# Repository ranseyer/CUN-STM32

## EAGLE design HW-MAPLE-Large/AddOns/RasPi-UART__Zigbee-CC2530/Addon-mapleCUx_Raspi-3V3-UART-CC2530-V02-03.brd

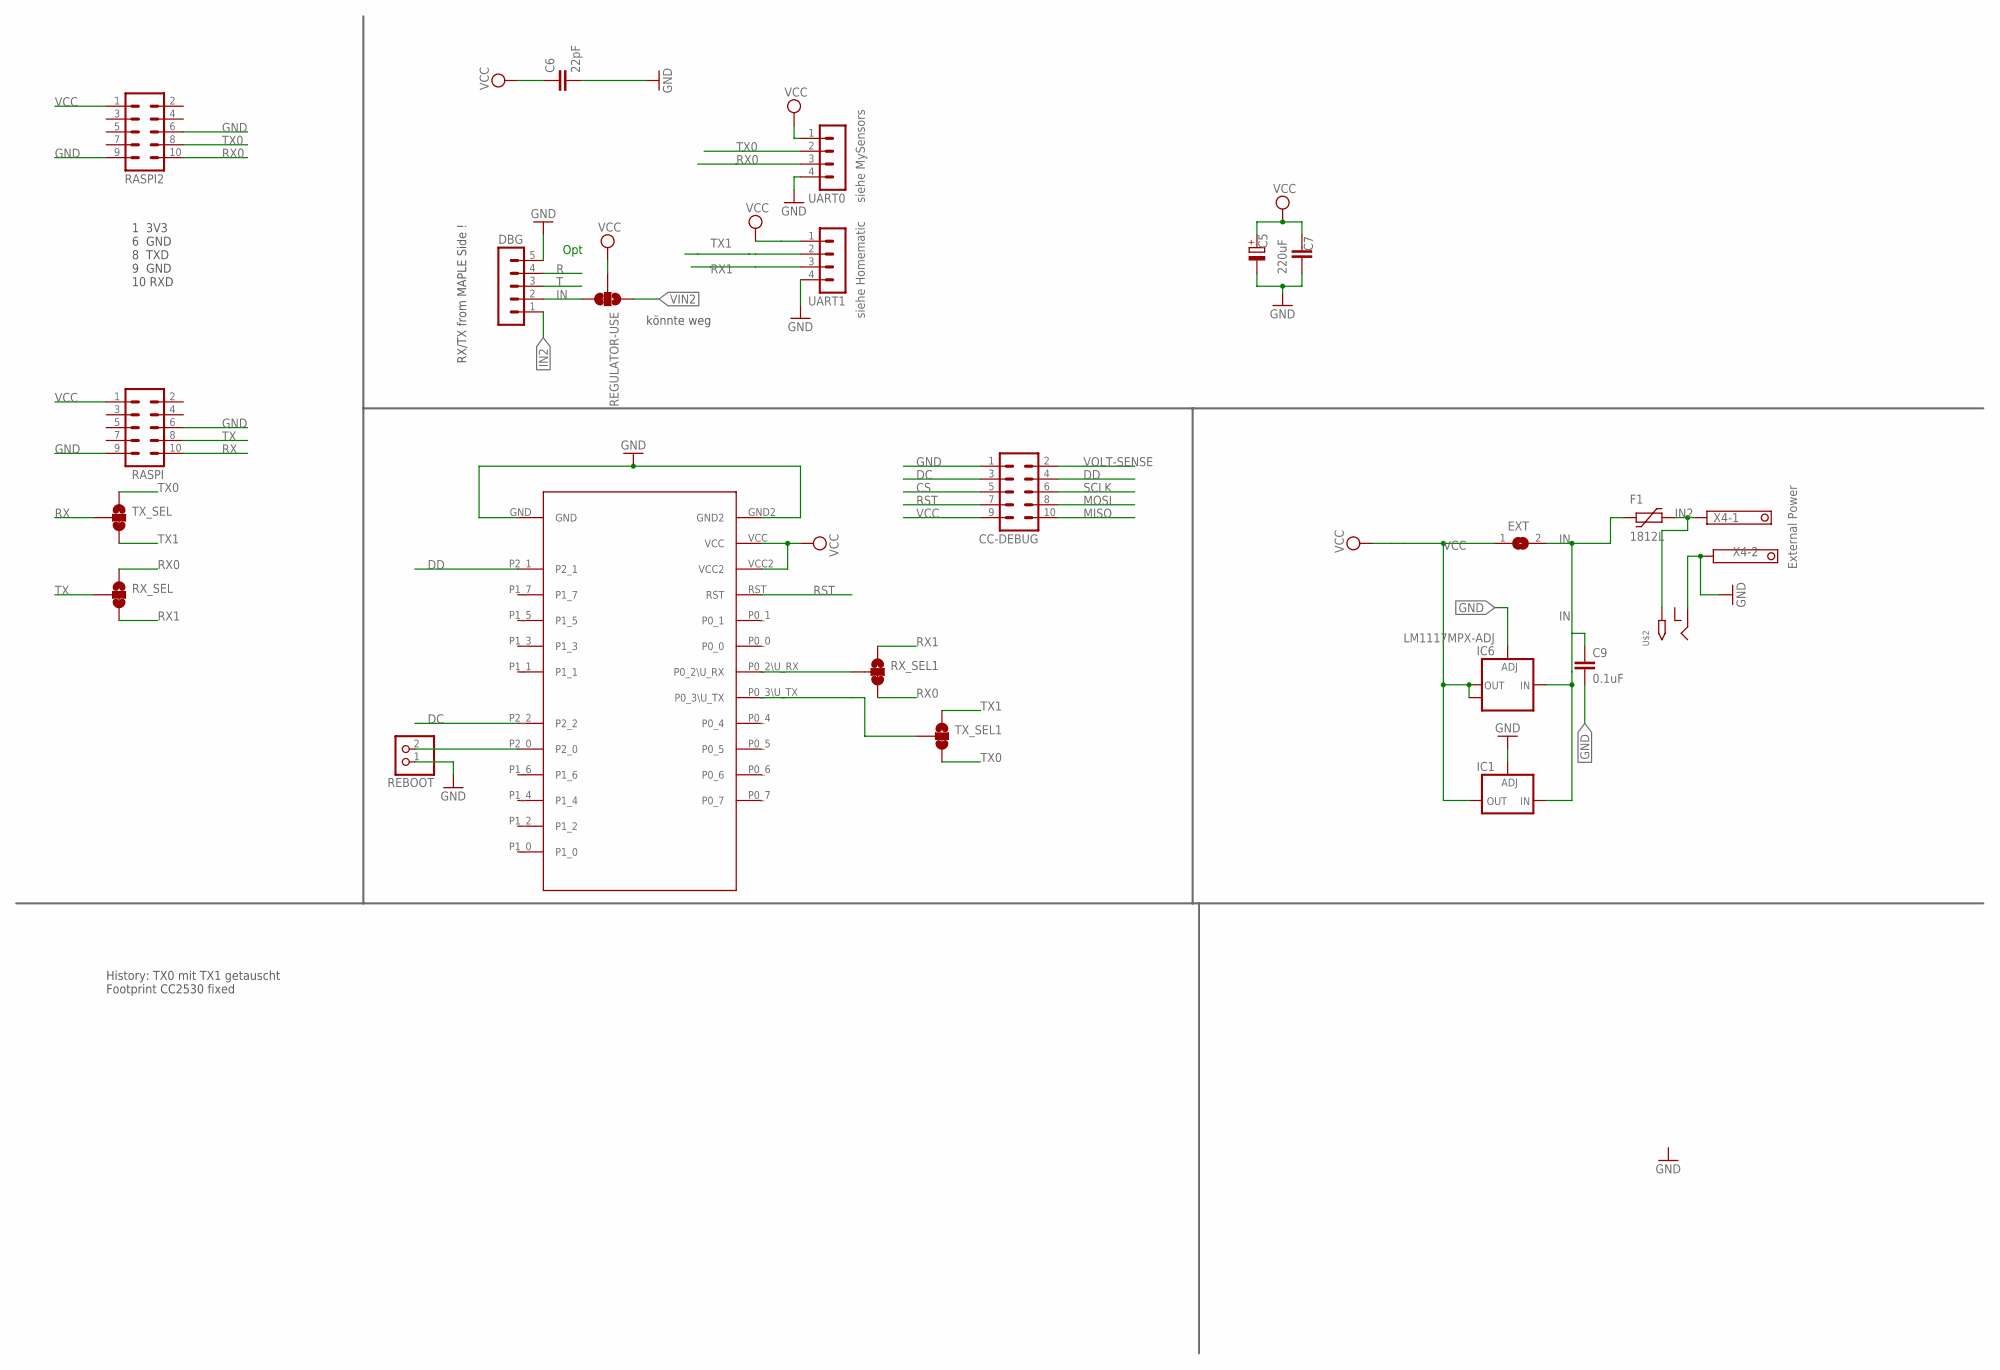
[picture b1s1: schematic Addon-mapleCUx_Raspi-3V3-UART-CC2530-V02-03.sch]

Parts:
C5: 220uF; E5-8,5
C6: 22pF; C0805
C7: C-EUC1812; C1812
C9: 0.1uF; C1206
CC-DEBUG: MA05-2
DBG: MA05-1
EXT: SJ
F1: 1812L
IC1: LD117ADT50TR; DPACK
IC6: LM1117MPX-ADJ; SOT223
RASPI, RASPI2: MA05-2
REBOOT: PINHD-1X2; 1X02
REGULATOR-USE: JUMPER-SMT_3_1-NC_TRACE_SILK; SMT-JUMPER_3_1-NC_TRACE_SILK
RX_SEL, RX_SEL1: JUMPER-SMT_3_1-NC_TRACE_SILK; SMT-JUMPER_3_1-NC_TRACE_SILK
TX_SEL, TX_SEL1: JUMPER-SMT_3_1-NC_TRACE_SILK; SMT-JUMPER_3_1-NC_TRACE_SILK
U$2: 2.1MMJACKTHM; PJ-102A
U$3: CC2530_MODULE; CC2530_DIL
UART0, UART1: MA04-1
X4: 1751248

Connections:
CS: CC-DEBUG.5
DC: CC-DEBUG.3, U$3.P2_2
DD: CC-DEBUG.4, U$3.P2_1
GND: C5.-, C6.2, C7.1, C9.2, CC-DEBUG.1, DBG.5, IC1.1 (ADJ), IC6.1 (ADJ), RASPI.6, RASPI.9, RASPI2.6, RASPI2.9, REBOOT.1, U$2.RING, U$3.GND, U$3.GND2, UART0.4, UART1.4, X4.2
IN: C9.1, DBG.2, EXT.2, F1.P$1 (1), IC1.3 (IN), IC6.3 (IN), REGULATOR-USE.3
IN2: DBG.1, F1.P$2 (2), U$2.TIP, X4.1
MISO: CC-DEBUG.10
MOSI: CC-DEBUG.8
unnamed: REBOOT.2, U$3.P2_0
unnamed: RX_SEL1.2, U$3.P0_2\U_RX
unnamed: TX_SEL1.2, U$3.P0_3\U_TX
R: DBG.4
RST: CC-DEBUG.7, U$3.RST
RX: RASPI.10, TX_SEL.2
RX0: RASPI2.10, RX_SEL.1, RX_SEL1.3, UART0.3
RX1: RX_SEL.3, RX_SEL1.1, UART1.3
SCLK: CC-DEBUG.6
T: DBG.3
TX: RASPI.8, RX_SEL.2
TX0: RASPI2.8, TX_SEL.1, TX_SEL1.3, UART0.2
TX1: TX_SEL.3, TX_SEL1.1, UART1.2
VCC: C5.+, C6.1, C7.2, CC-DEBUG.9, EXT.1, IC1.4 (OUT), IC6.2 (OUT), IC6.TAB (OUT1), RASPI.1, RASPI2.1, REGULATOR-USE.2, U$3.VCC, U$3.VCC2, UART0.1, UART1.1
VIN2: REGULATOR-USE.1
VOLT-SENSE: CC-DEBUG.2

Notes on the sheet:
Opt
siehe Homematic
siehe MySensors
1 3V3 6 GND 8 TXD 9 GND 10 RXD
RX/TX from MAPLE Side !
External Power
könnte weg
History: TX0 mit TX1 getauscht Footprint CC2530 fixed

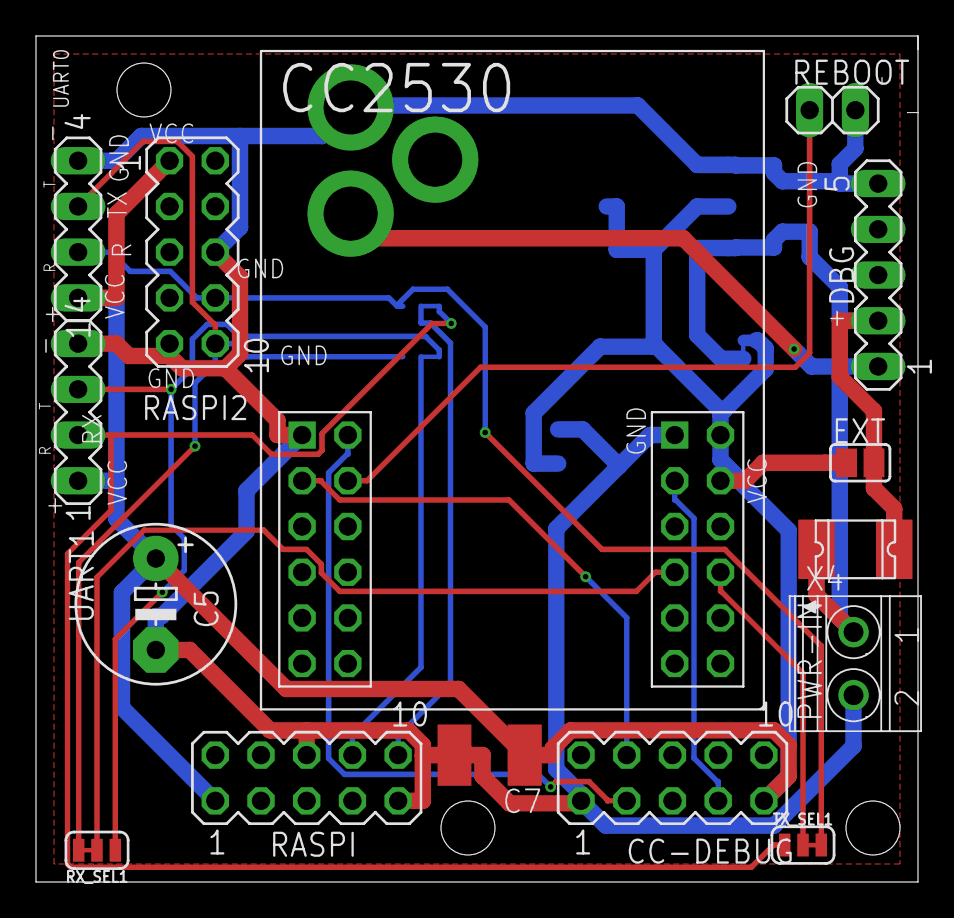
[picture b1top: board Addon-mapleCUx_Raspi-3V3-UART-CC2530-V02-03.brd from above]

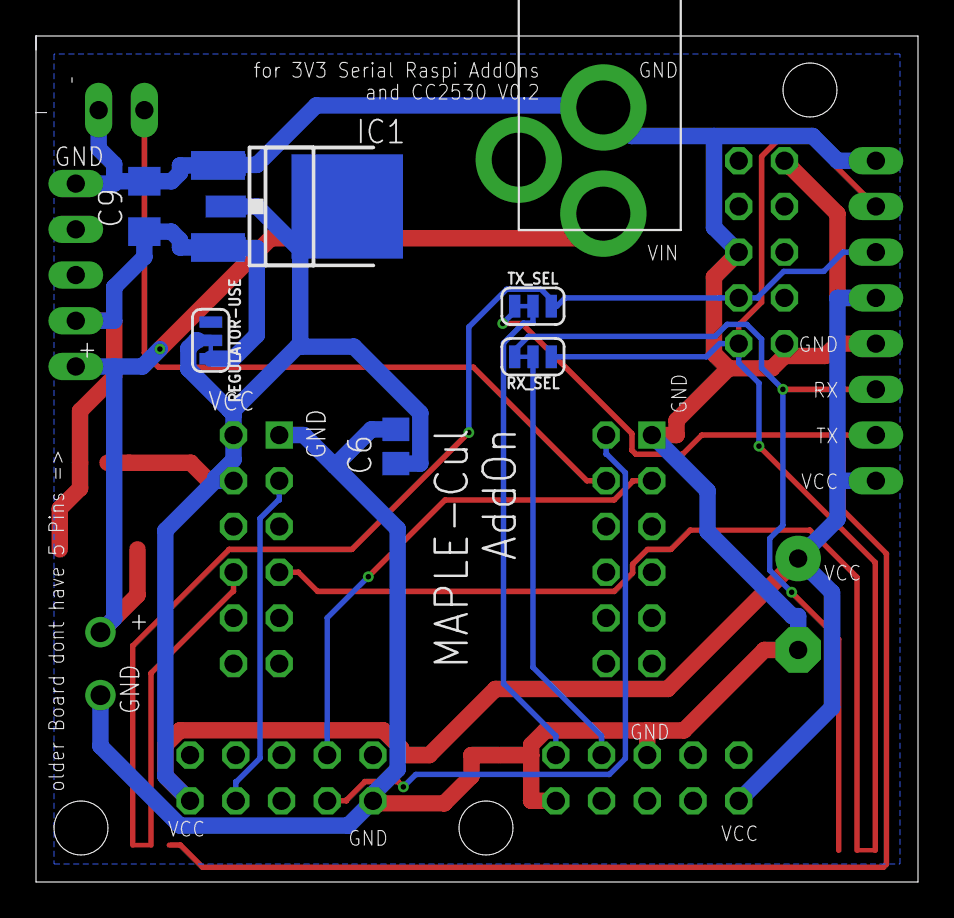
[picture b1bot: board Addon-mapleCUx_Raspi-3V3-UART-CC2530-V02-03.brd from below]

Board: 2 copper layers, 49.0 x 47.0 mm, 23 parts (8 on the bottom side), 16 nets.

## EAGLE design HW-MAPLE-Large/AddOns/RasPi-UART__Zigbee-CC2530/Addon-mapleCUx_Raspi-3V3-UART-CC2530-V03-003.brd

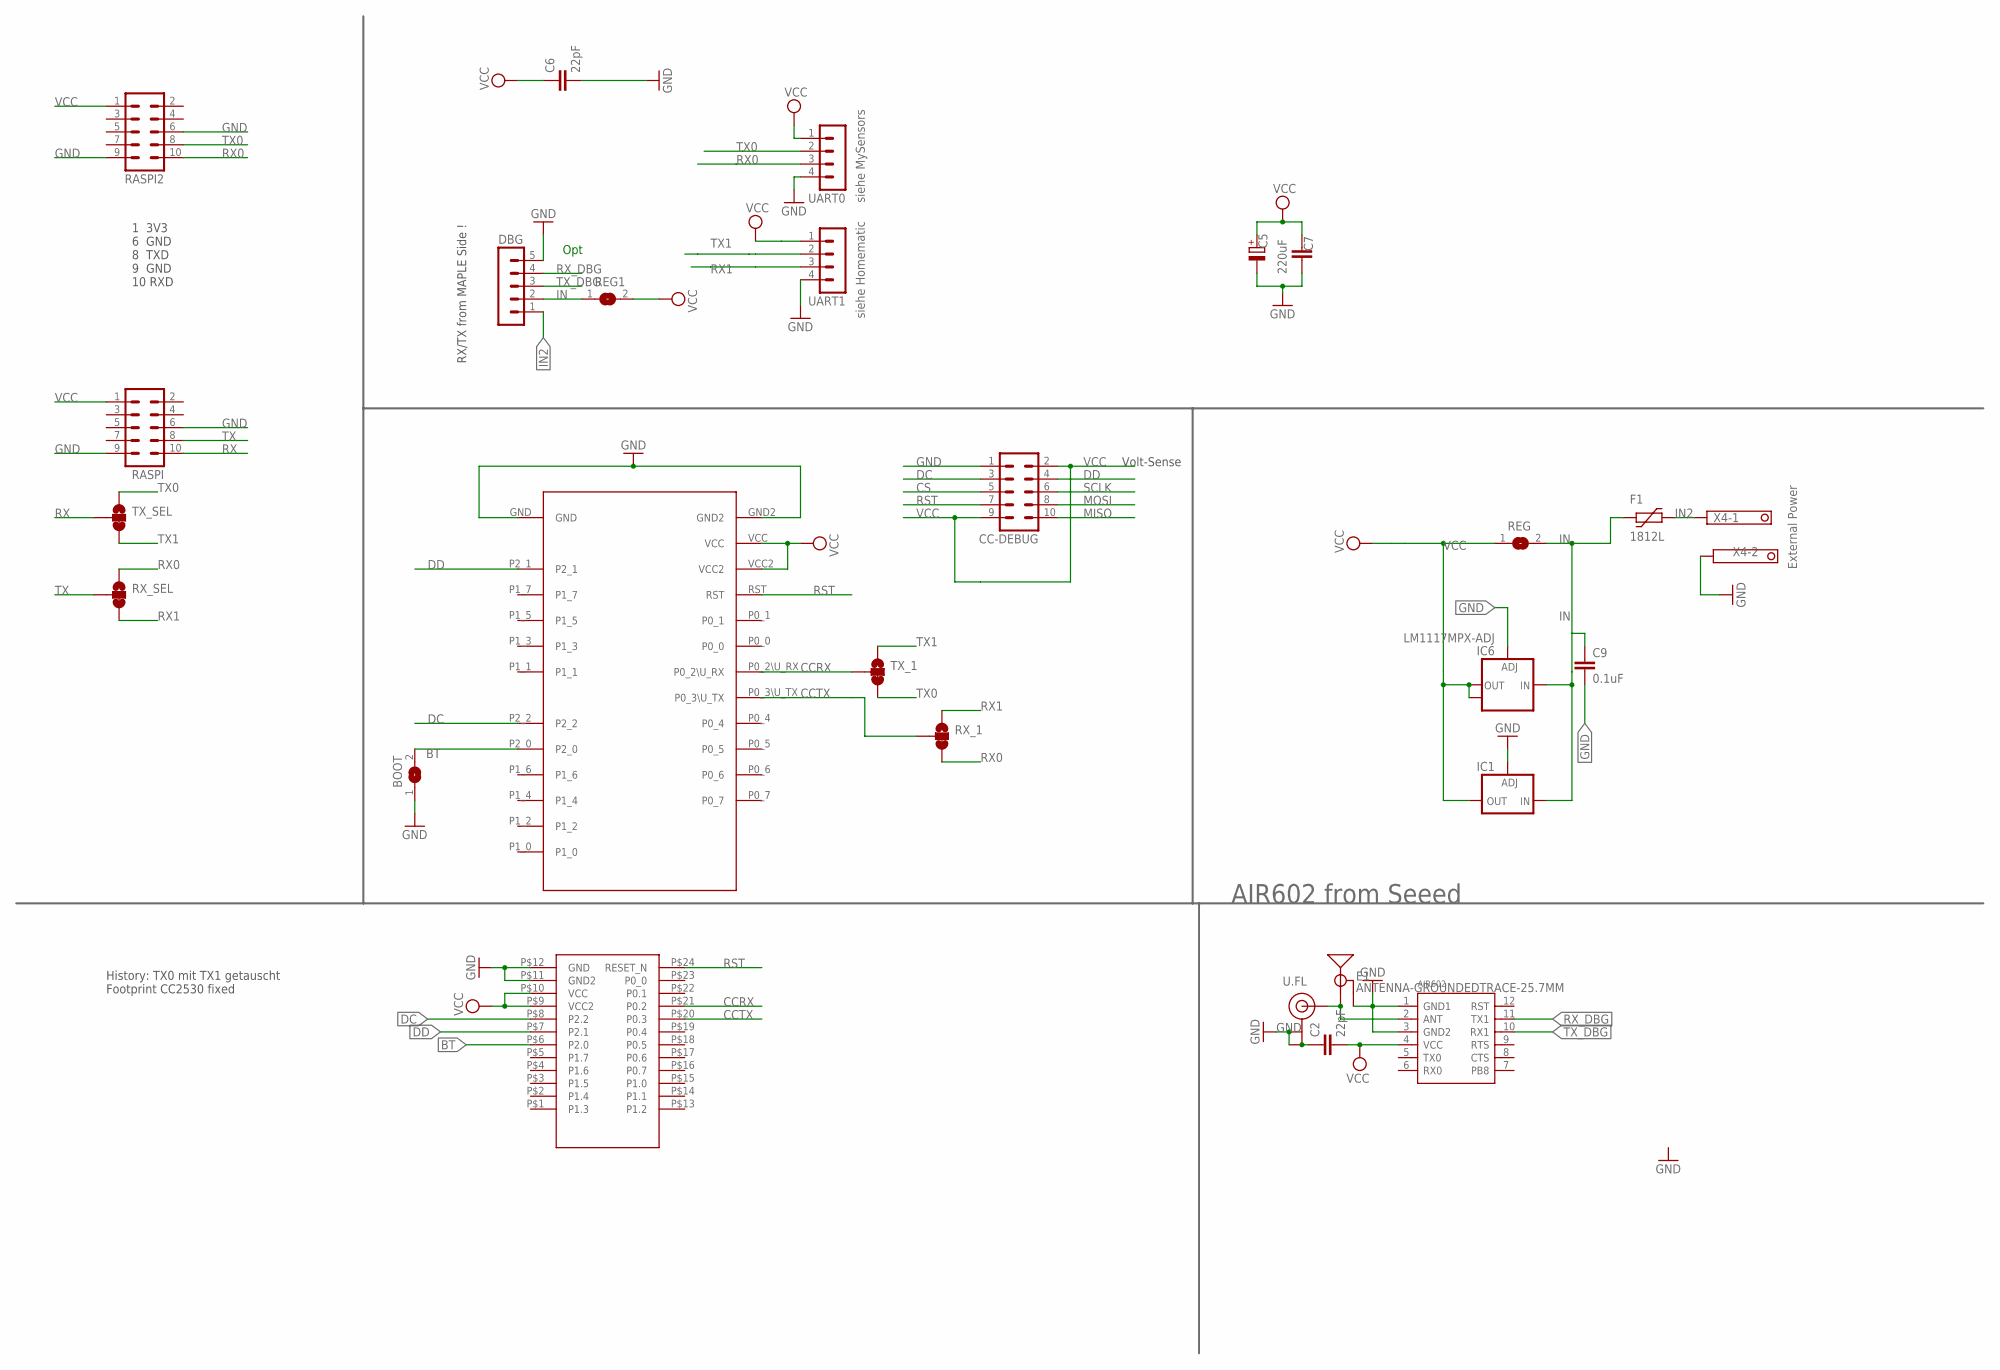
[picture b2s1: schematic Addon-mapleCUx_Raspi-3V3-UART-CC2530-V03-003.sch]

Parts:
AIR602: AIR602; MODULE12P-2.0-10X12MM
BOOT: SJ
C2, C6: 22pF; C0805
C5: 220uF; E5-8,5
C7: C-EUC1812; C1812
C9: 0.1uF; C1206
CC-DEBUG: MA05-2
DBG: MA05-1
E1: ANTENNA-GROUNDEDTRACE-25.7MM; TRACE_ANTENNA_2.4GHZ_25.7MM
F1: 1812L
IC1: LD117ADT50TR; DPACK
IC6: LM1117MPX-ADJ; SOT223
RASPI, RASPI2: MA05-2
REG, REG1: SJ
RX_1: JUMPER-SMT_3_1-NC_TRACE_SILK; SMT-JUMPER_3_1-NC_TRACE_SILK
RX_SEL: JUMPER-SMT_3_1-NC_TRACE_SILK; SMT-JUMPER_3_1-NC_TRACE_SILK
TX_1: JUMPER-SMT_3_1-NC_TRACE_SILK; SMT-JUMPER_3_1-NC_TRACE_SILK
TX_SEL: JUMPER-SMT_3_1-NC_TRACE_SILK; SMT-JUMPER_3_1-NC_TRACE_SILK
U$1: CC2530CC2530PA; CC2530PA
U$3: CC2530_MODULE; CC2530_DIL
U.FL: U.FL
UART0, UART1: MA04-1
X4: 1751248

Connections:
BT: BOOT.2, U$1.P$6 (P2.0), U$3.P2_0
CCRX: TX_1.2, U$1.P$21 (P0.2), U$3.P0_2\U_RX
CCTX: RX_1.2, U$1.P$20 (P0.3), U$3.P0_3\U_TX
CS: CC-DEBUG.5
DC: CC-DEBUG.3, U$1.P$8 (P2.2), U$3.P2_2
DD: CC-DEBUG.4, U$1.P$7 (P2.1), U$3.P2_1
GND: AIR602.1 (GND1), AIR602.3 (GND2), BOOT.1, C2.1, C5.-, C6.2, C7.1, C9.2, CC-DEBUG.1, DBG.5, E1.GND, E1.GND2 (GND), IC1.1 (ADJ), IC6.1 (ADJ), RASPI.6, RASPI.9, RASPI2.6, RASPI2.9, U$1.P$11 (GND2), U$1.P$12 (GND), U$3.GND, U$3.GND2, U.FL.1 (GND), U.FL.2 (GND), UART0.4, UART1.4, X4.2
IN: C9.1, DBG.2, F1.P$1 (1), IC1.3 (IN), IC6.3 (IN), REG.2, REG1.1
IN2: DBG.1, F1.P$2 (2), X4.1
MISO: CC-DEBUG.10
MOSI: CC-DEBUG.8
unnamed: AIR602.2 (ANT), E1.ANT (SIGNAL), U.FL.FEED (SIGNAL)
RST: CC-DEBUG.7, U$1.P$24 (RESET_N), U$3.RST
RX: RASPI.10, TX_SEL.2
RX0: RASPI2.10, RX_1.3, RX_SEL.1, UART0.3
RX1: RX_1.1, RX_SEL.3, UART1.3
RX_DBG: AIR602.11 (TX1), DBG.4
SCLK: CC-DEBUG.6
TX: RASPI.8, RX_SEL.2
TX0: RASPI2.8, TX_1.3, TX_SEL.1, UART0.2
TX1: TX_1.1, TX_SEL.3, UART1.2
TX_DBG: AIR602.10 (RX1), DBG.3
VCC: AIR602.4 (VCC), C2.2, C5.+, C6.1, C7.2, CC-DEBUG.2, CC-DEBUG.9, IC1.4 (OUT), IC6.2 (OUT), IC6.TAB (OUT1), RASPI.1, RASPI2.1, REG.1, REG1.2, U$1.P$9 (VCC2), U$1.P$10 (VCC), U$3.VCC, U$3.VCC2, UART0.1, UART1.1

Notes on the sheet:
Opt
siehe Homematic
siehe MySensors
1 3V3 6 GND 8 TXD 9 GND 10 RXD
RX/TX from MAPLE Side !
External Power
History: TX0 mit TX1 getauscht Footprint CC2530 fixed
Volt-Sense
AIR602 from Seeed

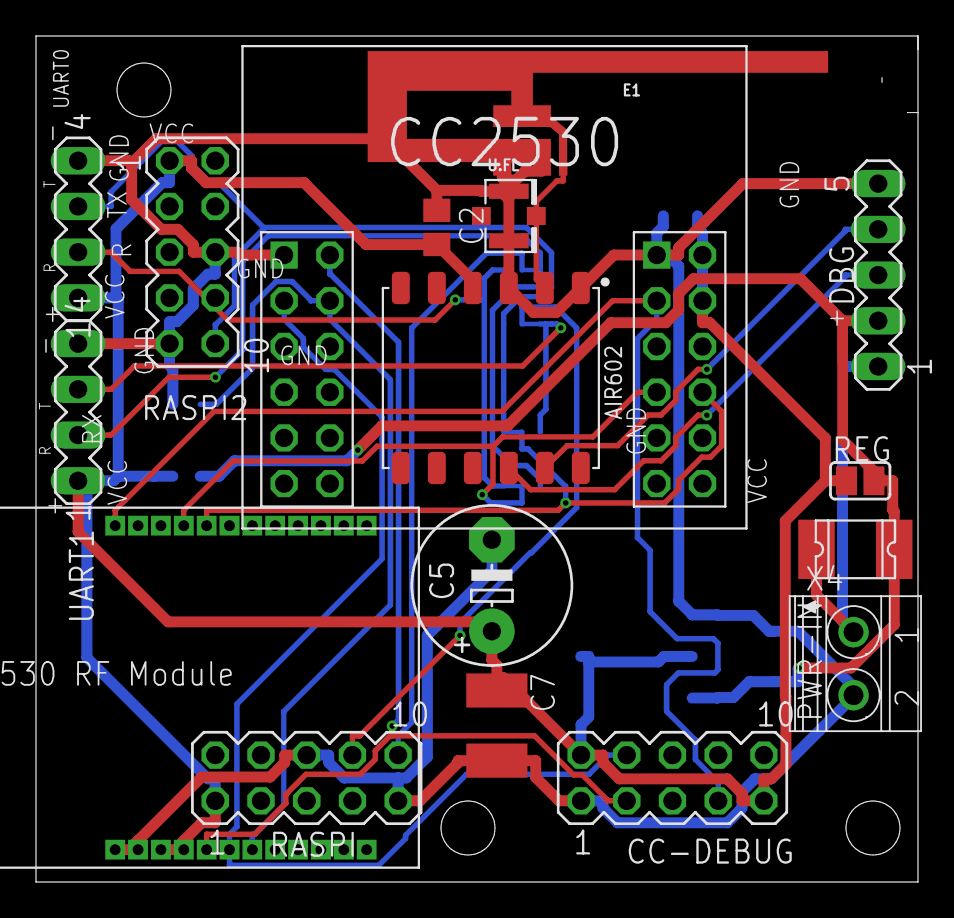
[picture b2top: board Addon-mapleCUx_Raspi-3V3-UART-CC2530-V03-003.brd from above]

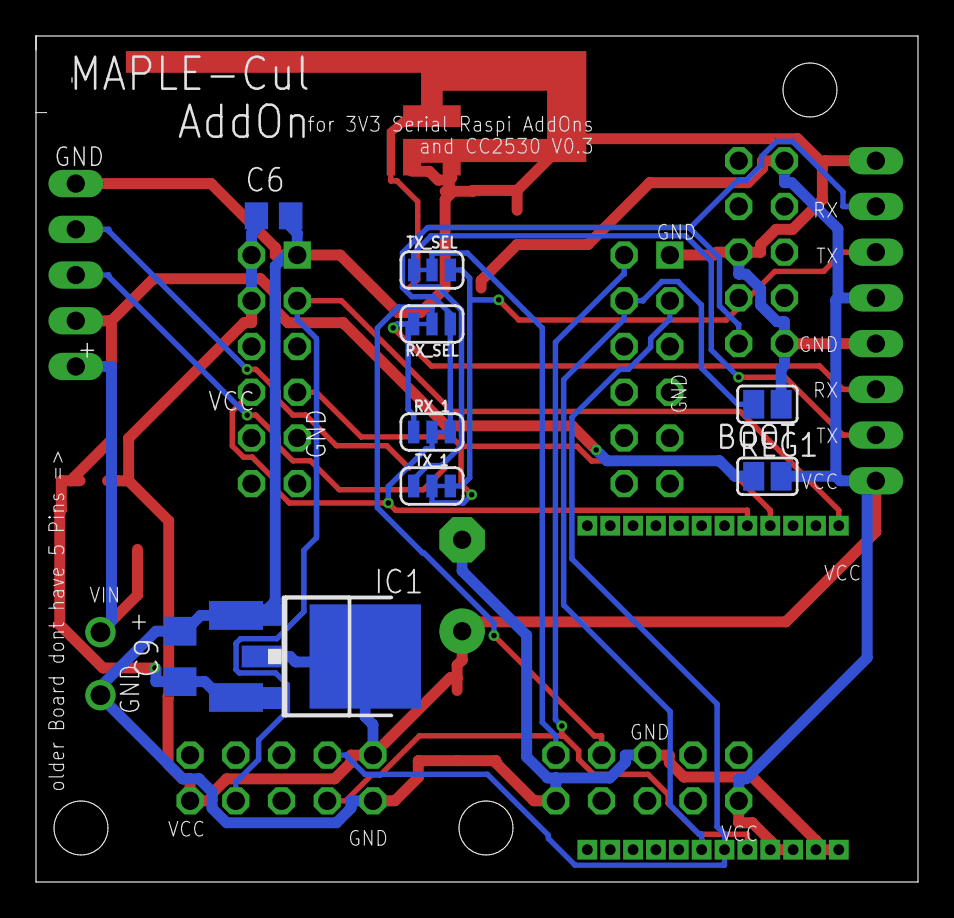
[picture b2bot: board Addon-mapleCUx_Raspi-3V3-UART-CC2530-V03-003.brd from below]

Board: 2 copper layers, 49.0 x 47.0 mm, 27 parts (10 on the bottom side), 19 nets.

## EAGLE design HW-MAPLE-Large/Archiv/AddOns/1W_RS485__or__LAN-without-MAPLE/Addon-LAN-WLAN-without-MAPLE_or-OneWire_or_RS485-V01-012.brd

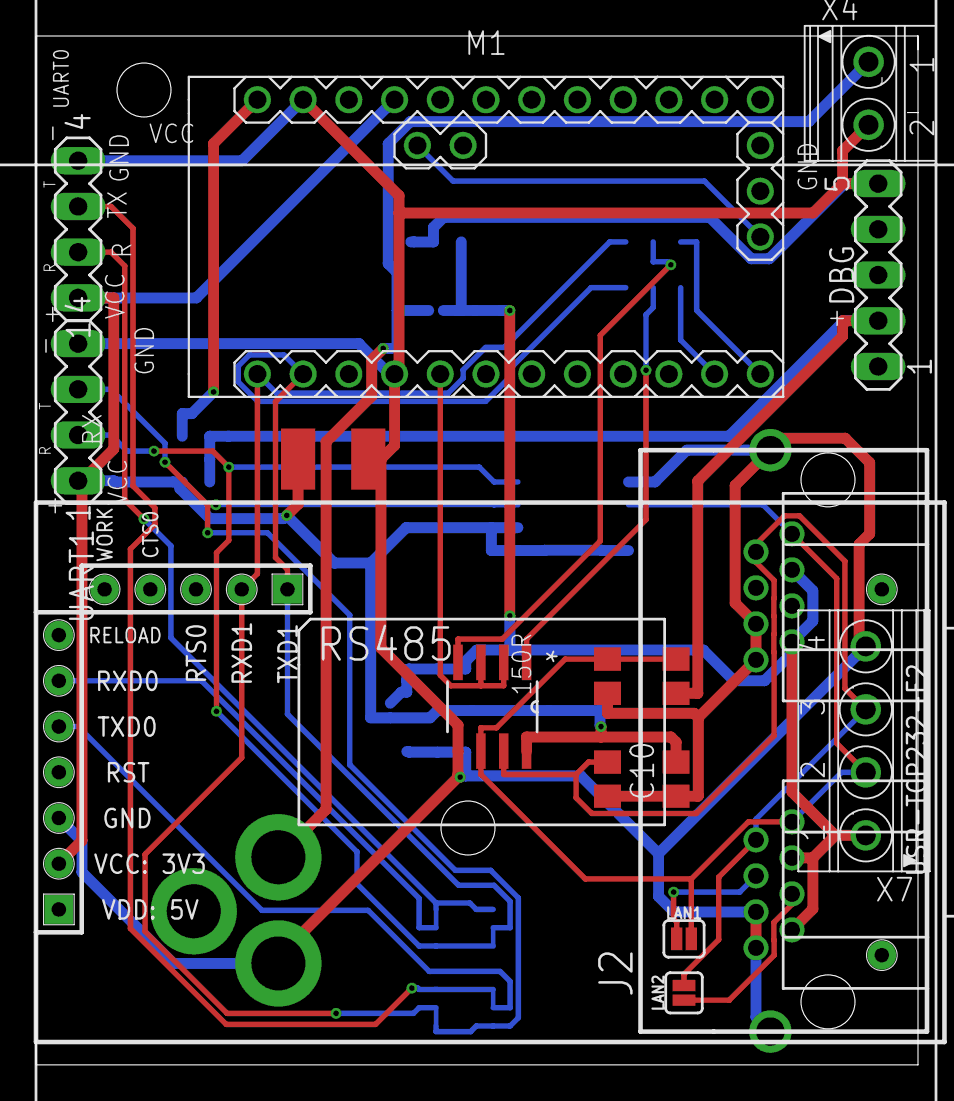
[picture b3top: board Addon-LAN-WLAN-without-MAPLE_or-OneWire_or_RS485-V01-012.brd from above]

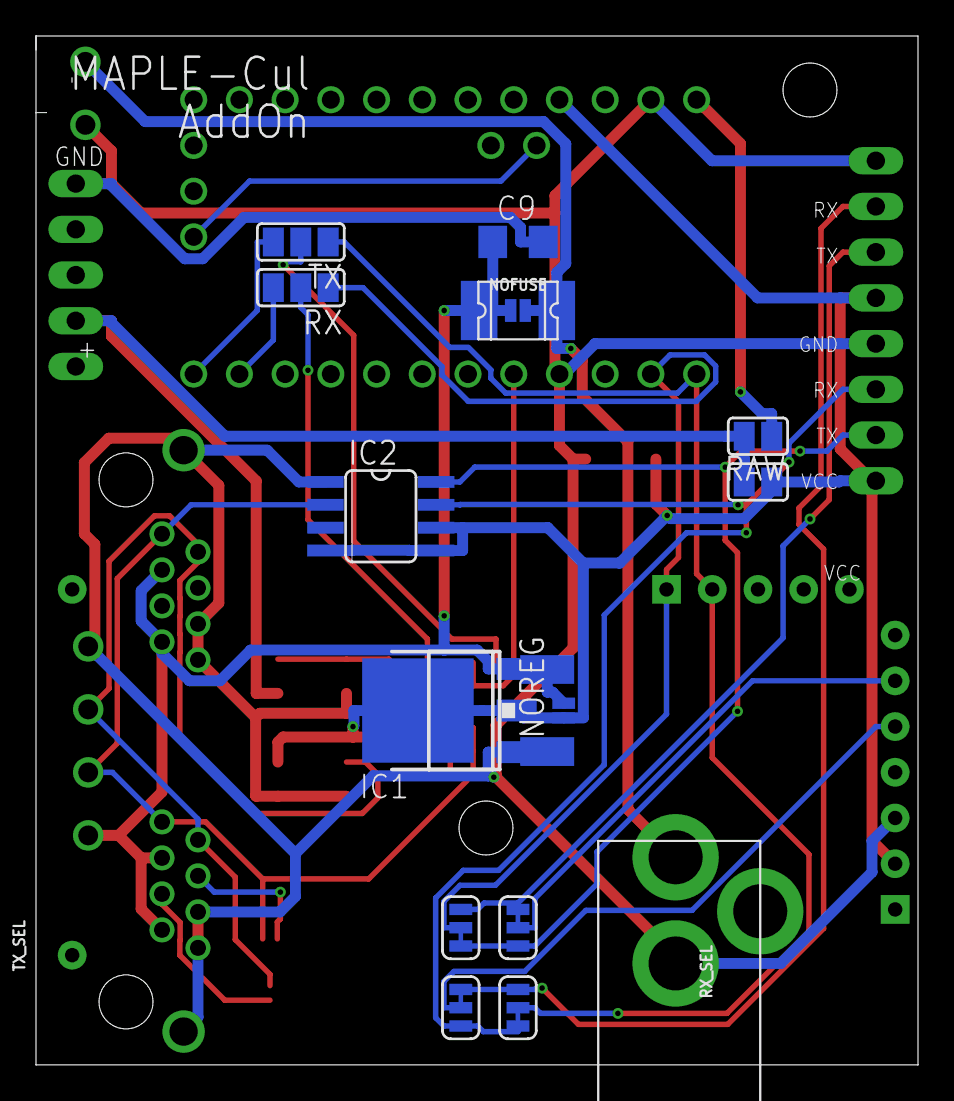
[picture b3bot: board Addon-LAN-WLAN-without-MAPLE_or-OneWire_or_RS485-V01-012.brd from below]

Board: 2 copper layers, 49.0 x 57.2 mm, 32 parts (16 on the bottom side), 24 nets.

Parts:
C7: C1812
C9: 0.1uF; C1206
C10: 22p; C0805
DBG: MA05-1
F1: 1812L
IC1: LD117ADT50TR; DPACK
IC2: DS2480B; SO08
IC6: LM1117MPX-ADJ; SOT223
J2: RJ45_2X_S
LAN1, LAN2: JUMPER-SMT_2_NC_PASTE_SILK; SMT-JUMPER_2_NC_PASTE_SILK
M1: ARDUINO-PRO-MINI-3.3V#NP; ARDUINO-PRO-MINI#NP
NOFUSE: JUMPER-SMT_2_NC_PASTE_NO-SILK; SMT-JUMPER_2_NC_PASTE_NO-SILK
NOREG: JUMPER-SMT_2_NC_PASTE_NO-SILK; SMT-JUMPER_2_NC_PASTE_NO-SILK
R4: 5K6; R0805
R5: 22K; R0805
R6: 4K7; R0805
RAW: SJ
REG1: SJ
RS485: MAX487ECSA+; SOIC127P600X175-8N
RX: SJ_2
RX_1: JUMPER-SMT_3_1-NC_TRACE_SILK; SMT-JUMPER_3_1-NC_TRACE_SILK
RX_SEL: JUMPER-SMT_3_1-NC_TRACE_SILK; SMT-JUMPER_3_1-NC_TRACE_SILK
TX: SJ_2
TX_1: JUMPER-SMT_3_1-NC_TRACE_SILK; SMT-JUMPER_3_1-NC_TRACE_SILK
TX_SEL: JUMPER-SMT_3_1-NC_TRACE_SILK; SMT-JUMPER_3_1-NC_TRACE_SILK
U$2: 2.1MMJACKTHM; PJ-102A
U$5: USR-TCP232-E2
UART0, UART1: MA04-1
X4: 1751248
X7: 1751264

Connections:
4: J2.1-4, LAN1.1
5: J2.1-5, LAN2.1
A: IC2.2, J2.1-1, J2.2-1, LAN1.2, R4.2, R5.2, RS485.6, X7.2
A5: M1.J2.2, M1.J3.1
B: J2.1-2, J2.2-2, LAN2.2, R6.1, RS485.7, X7.3
D8: M1.J7.2, RX.3
D9: M1.J7.1, TX.3
DI1: RS485.4, TX.2
GND: C7.1, C9.2, C10.1, DBG.5, IC1.1, IC2.1, IC6.1, J2.1-6, J2.1-8, J2.2-6, J2.2-8, J2.G1, J2.G3, M1.J6.2, M1.J7.9, R4.1, R6.2, RS485.5, U$2.RING, U$5.GND, UART0.4, UART1.4, X4.2, X7.4
IN: DBG.2, R5.1, RAW.2, REG1.1
IRQ: M1.J7.8, RS485.2, RS485.3
RAW1: M1.J6.1, RAW.1
RO: RS485.1, RX.2
RX: M1.J7.11, RX.1, TX_SEL.2, U$5.TXD1
RX0: RX_1.3, RX_SEL.1, UART0.3
RX1: IC2.7, RX_1.1, RX_SEL.3, UART1.3
TX: M1.J7.12, RX_SEL.2, TX.1, U$5.RXD1
TX0: TX_1.3, TX_SEL.1, UART0.2
TX1: IC2.8, TX_1.1, TX_SEL.3, UART1.2
USRRX0: TX_1.2, U$5.RXD0
USRTX0: RX_1.2, U$5.TXD0
VCC: C7.2, C10.2, IC1.4, IC2.4, IC2.5, IC2.6, IC6.2, IC6.TAB, M1.J6.4, NOREG.1, REG1.2, RS485.8, U$5.3.3V, UART0.1, UART1.1
VIN: C9.1, F1.P$1, IC1.3, IC6.3, J2.1-3, J2.1-7, J2.2-3, J2.2-7, NOFUSE.1, NOREG.2, X7.1
VINPUT: F1.P$2, NOFUSE.2, U$2.TIP, X4.1

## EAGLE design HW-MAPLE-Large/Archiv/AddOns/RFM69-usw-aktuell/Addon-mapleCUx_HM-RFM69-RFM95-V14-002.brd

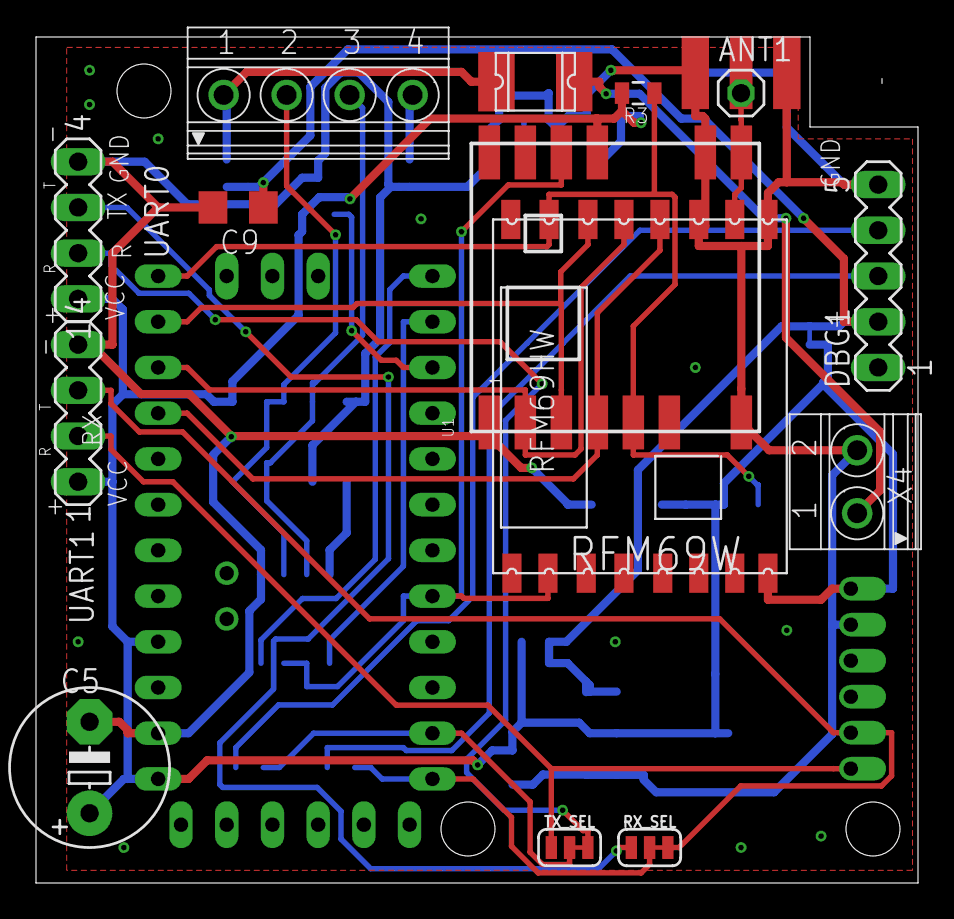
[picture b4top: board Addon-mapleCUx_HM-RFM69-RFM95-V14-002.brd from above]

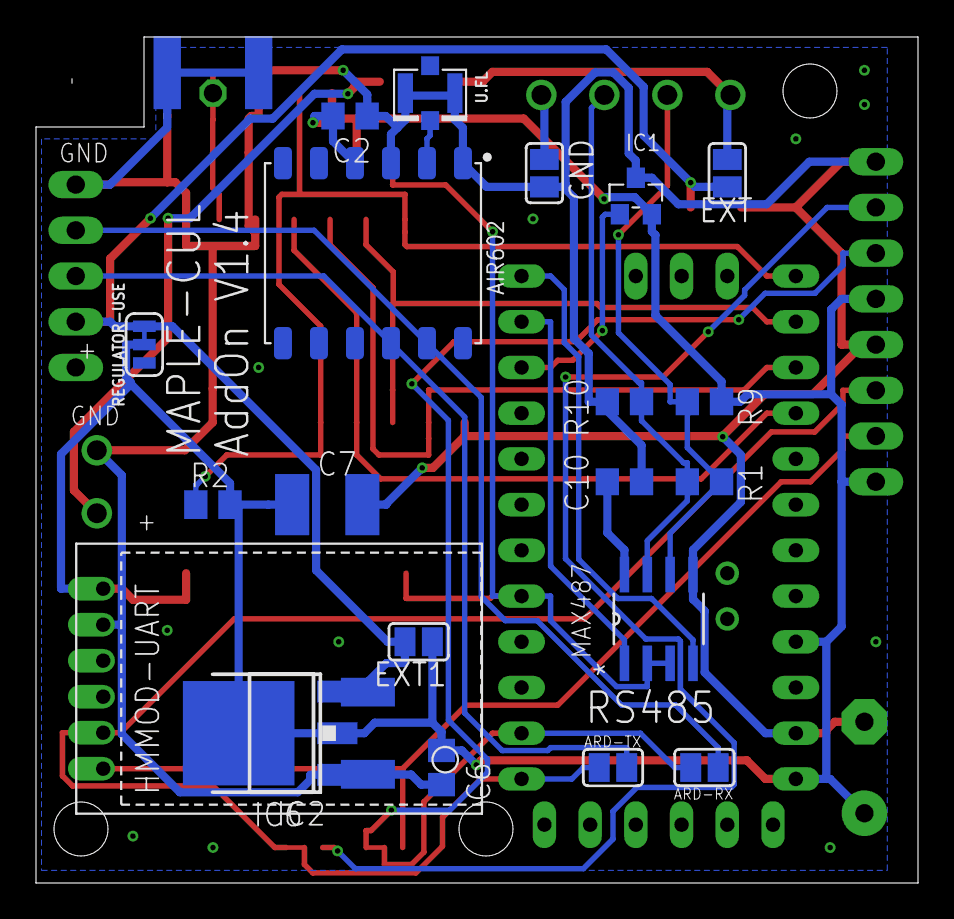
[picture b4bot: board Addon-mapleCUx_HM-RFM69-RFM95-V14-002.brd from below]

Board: 2 copper layers, 49.0 x 47.0 mm, 37 parts (21 on the bottom side), 27 nets.

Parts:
AIR602: MODULE12P-2.0-10X12MM
ANT1: 1X01
ARD-RX: SJ
ARD-TX: SJ
C2, C6: 22pF; C0805
C5: 220uF; E5-8,5
C7: C1812
C9: 0.1uF; C1206
C10: 22p; C0805
DBG1: MA05-1
EXT, EXT1: SJ
F1: 1812L
GND: SJ
HMMOD-UART: HM-MOD-UARTDIL; HM-MOD-UART-DIL
IC1: ATSHA204A; SOT23
IC2: LD117ADT50TR; DPACK
IC6: LM1117MPX-ADJ; SOT223
R1: 150R; R0805
R2: 10k; M0805
R3: 10k; 0805
R9, R10: 330R; R0805
REGULATOR-USE: JUMPER-SMT_3_1-NC_TRACE_SILK; SMT-JUMPER_3_1-NC_TRACE_SILK
RFM69W: RFM69HW; RFM
RS1: MAX487ECSA+; SOIC127P600X175-8N
RX_SEL: JUMPER-SMT_3_1-NC_TRACE_SILK; SMT-JUMPER_3_1-NC_TRACE_SILK
TX_SEL: JUMPER-SMT_3_1-NC_TRACE_SILK; SMT-JUMPER_3_1-NC_TRACE_SILK
U1: RFM69HCW; RFM69HCW-XXXS2
U$2: ABK-PRO-MINI
U.FL: U.FL
UART0, UART1: MA04-1
X2: SMA_EDGELAUNCH
X4: 1751248
X7: 1751264

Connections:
1W: R1.1, R9.2, RS1.6, X7.2
2W: R1.2, R10.1, RS1.7, X7.3
AN: AIR602.2, U.FL.FEED
ANT: ANT1.1, RFM69W.ANT, U1.ANT, X2.P
CE-A: RS1.4, U$2.D9
CSN-A: R2.1, R3.1, RFM69W.NSS, U1.NSS, U$2.D10
D7-ATSHA-ARDU: IC1.1, U$2.D7
EXT: EXT.2, F1.P$1, X7.1
GD: GND.2, X7.4
GND: AIR602.1, AIR602.3, C2.1, C5.-, C6.2, C7.1, C9.2, C10.1, DBG1.5, GND.1, HMMOD-UART.2, IC1.3, IC2.1, IC6.1, R10.2, RFM69W.GNDA, RFM69W.GNDB, RS1.5, U1.GND_1, U1.GND_2, U1.GND_3, U$2.GND, U.FL.1, U.FL.2, UART0.4, UART1.4, X2.GND@1, X2.GND@2, X2.GND@3, X2.GND@4, X4.2
IN: C9.1, DBG1.2, EXT.1, EXT1.2, IC2.3, IC6.3, REGULATOR-USE.3
IRQ-A: RFM69W.DIO0, RS1.2, RS1.3, U1.DIO0, U$2.D2
MISO-A: RFM69W.MISO, U1.MISO, U$2.D12
MOSI-A: RFM69W.MOSI, U1.MOSI, U$2.D11
unnamed: F1.P$2, X4.1
RO-A: RS1.1, U$2.D8
RX: ARD-RX.2, TX_SEL.2, U$2.RX1
RX0: RX_SEL.1, UART0.3
RX1: HMMOD-UART.5, RX_SEL.3, UART1.3
RX_DBG: AIR602.11, ARD-RX.1, DBG1.4
SCK-A: RFM69W.SCK, U1.SCK, U$2.D13
TX: ARD-TX.1, RX_SEL.2, U$2.TX0
TX0: TX_SEL.3, UART0.2
TX1: HMMOD-UART.6, TX_SEL.1, UART1.2
TX_DBG: AIR602.10, ARD-TX.2, DBG1.3
VCC: AIR602.4, C2.2, C5.+, C6.1, C7.2, EXT1.1, HMMOD-UART.1, IC1.2, IC2.4, IC6.2, IC6.TAB, R2.2, R3.2, R9.1, REGULATOR-USE.2, RFM69W.VCC, U1.3.3V, U$2.RAW, U$2.VCC, UART0.1, UART1.1
VDD: C10.2, RS1.8

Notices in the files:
parts and their libraries:
SparkFun-Jumpers: Licensing: Creative Commons ShareAlike 4.0 International - https://creativecommons.org/licenses/by-sa/4.0
diy-modules: Released under the Creative Commons Attribution 4.0 International License: http://creativecommons.org/licenses/by/4.0
